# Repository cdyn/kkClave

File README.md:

# kkClave ([wiki](https://github.com/cdyn/kkClave/wiki))
## [Korai Kitchen](https://www.koraikitchen.com/) Clave for yogurt incubation
#### Designed by [Jean Runnells](https://github.com/JERiv) @ [CDYN](https://github.com/cdyn)

This is a simple yougurt incubator that uses an arduino mega, a relay shield, and a space heater to make doi (yogurt) on a large scale in an upcycled beverege fridge. In this repository are: 
* [Fusion 360](../master/fusion) drawings for the power supply panel, the front panel, and an enclosure.
* [Eagle](../master/eagle) sketch of basic circuit diagram for logic and power supply including relevant shields
* [Arduino](../master/arduino) main program code

## See the [wiki](https://github.com/cdyn/kkClave/wiki) for installtion, fabrication, and use details.

## TODO:
*  implement ethernet
*  add cooling cycle features
*  handle clock overflow

[**Custom Dynamics**](https://www.customdyn.com) © [*GNU General Public License v3.0*](https://github.com/cdyn/kkClave/blob/master/LICENSE)

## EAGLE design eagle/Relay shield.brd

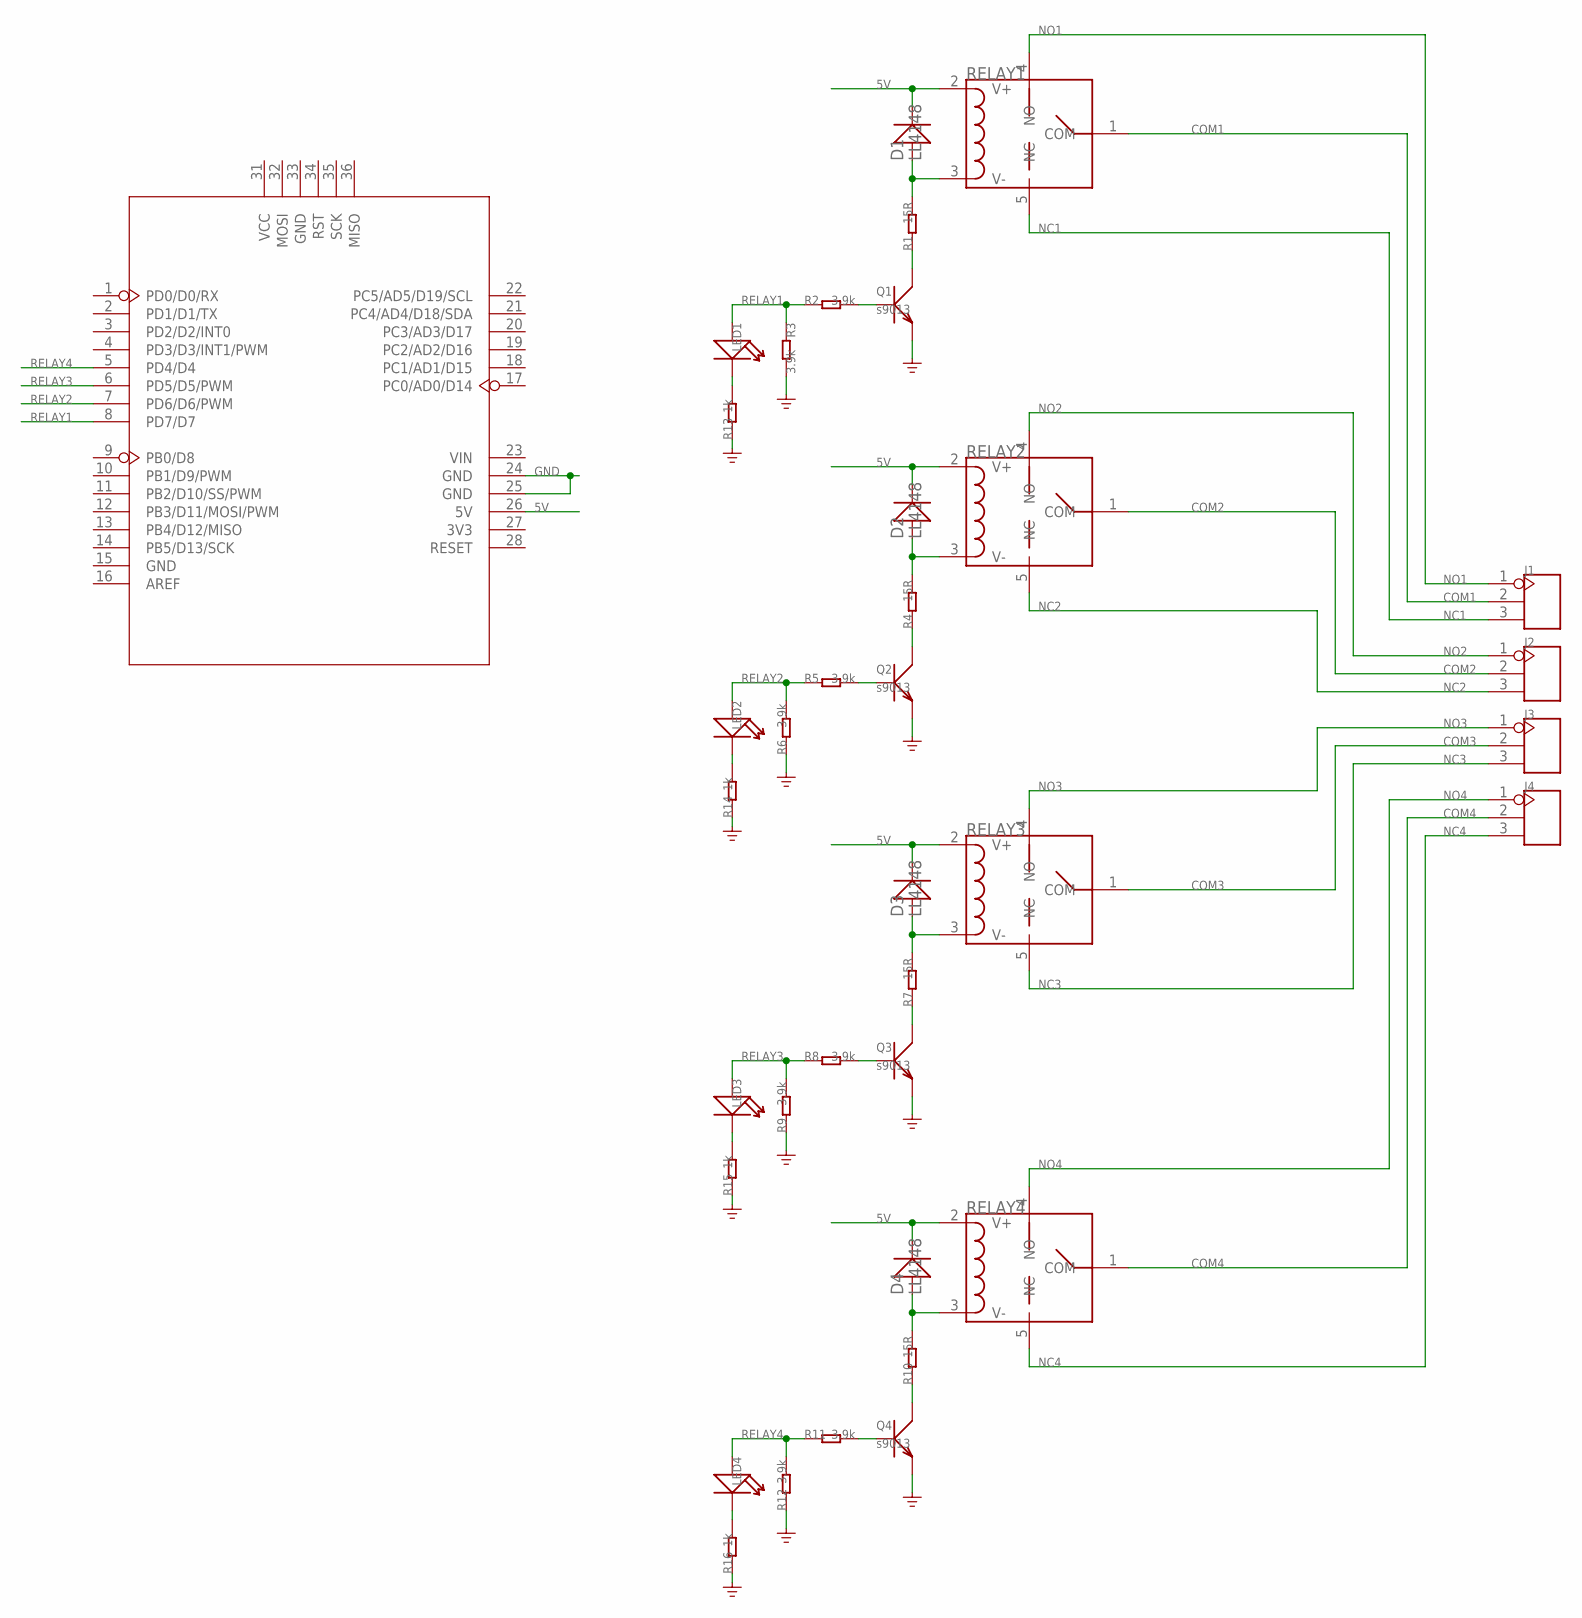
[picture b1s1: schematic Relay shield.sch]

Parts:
D1, D2, D3, D4: LL4148; D1206
J1, J2, J3, J4: SCREW-TERMINAL-3P'5.08'; 3P-5.08
LED1, LED2, LED3, LED4: LED'0603'; LED-0603
Q1, Q2, Q3, Q4: s9013; SOT23
R1, R4, R7, R10: 15R; R0603
R2, R3, R5, R6, R8, R9, R11, R12: 3.9k; R0603
R13, R14, R15, R16: 1k; R0603
RELAY1, RELAY2, RELAY3, RELAY4: RELAY-HLS8L-DC5V-S-C; 5P-19.0X15.5X15.8H
U1: ARDUINO'W/O-SILK'; ARDUINO-W/O-SILK

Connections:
5V: D1.-, D2.-, D3.-, D4.-, RELAY1.2 (V+), RELAY2.2 (V+), RELAY3.2 (V+), RELAY4.2 (V+), U1.26 (5V)
COM1: J1.2, RELAY1.1 (COM)
COM2: J2.2, RELAY2.1 (COM)
COM3: J3.2, RELAY3.1 (COM)
COM4: J4.2, RELAY4.1 (COM)
GND: Q1.2 (E), Q2.2 (E), Q3.2 (E), Q4.2 (E), R3.2, R6.1, R9.1, R12.1, R13.1, R14.1, R15.1, R16.1, U1.24 (GND), U1.25 (GND)
unnamed: D2.+, R4.2, RELAY2.3 (V-)
unnamed: D3.+, R7.2, RELAY3.3 (V-)
unnamed: D4.+, R10.2, RELAY4.3 (V-)
unnamed: Q1.3 (C), R1.1
unnamed: Q2.3 (C), R4.1
unnamed: Q4.1 (B), R11.2
unnamed: D1.+, R1.2, RELAY1.3 (V-)
unnamed: Q3.3 (C), R7.1
unnamed: Q4.3 (C), R10.1
unnamed: Q3.1 (B), R8.2
unnamed: LED1.-, R13.2
unnamed: LED2.-, R14.2
unnamed: LED3.-, R15.2
unnamed: LED4.-, R16.2
unnamed: Q2.1 (B), R5.2
unnamed: Q1.1 (B), R2.2
NC1: J1.3, RELAY1.5 (NC)
NC2: J2.3, RELAY2.5 (NC)
NC3: J3.3, RELAY3.5 (NC)
NC4: J4.3, RELAY4.5 (NC)
NO1: J1.1, RELAY1.4 (NO)
NO2: J2.1, RELAY2.4 (NO)
NO3: J3.1, RELAY3.4 (NO)
NO4: J4.1, RELAY4.4 (NO)
RELAY1: LED1.+, R2.1, R3.1, U1.8 (PD7/D7)
RELAY2: LED2.+, R5.1, R6.2, U1.7 (PD6/D6/PWM)
RELAY3: LED3.+, R8.1, R9.2, U1.6 (PD5/D5/PWM)
RELAY4: LED4.+, R11.1, R12.2, U1.5 (PD4/D4)

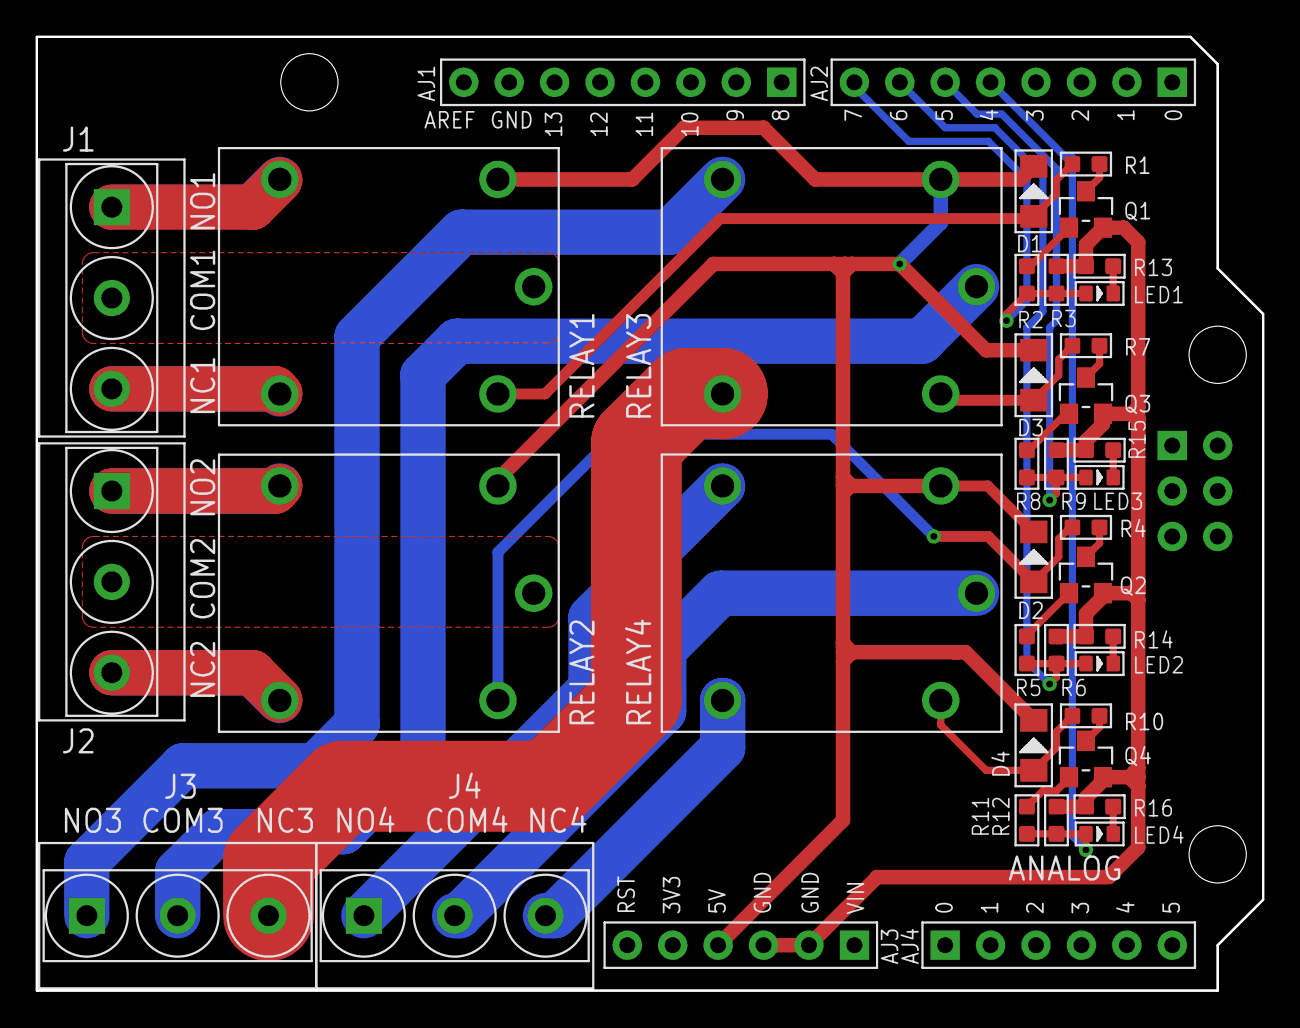
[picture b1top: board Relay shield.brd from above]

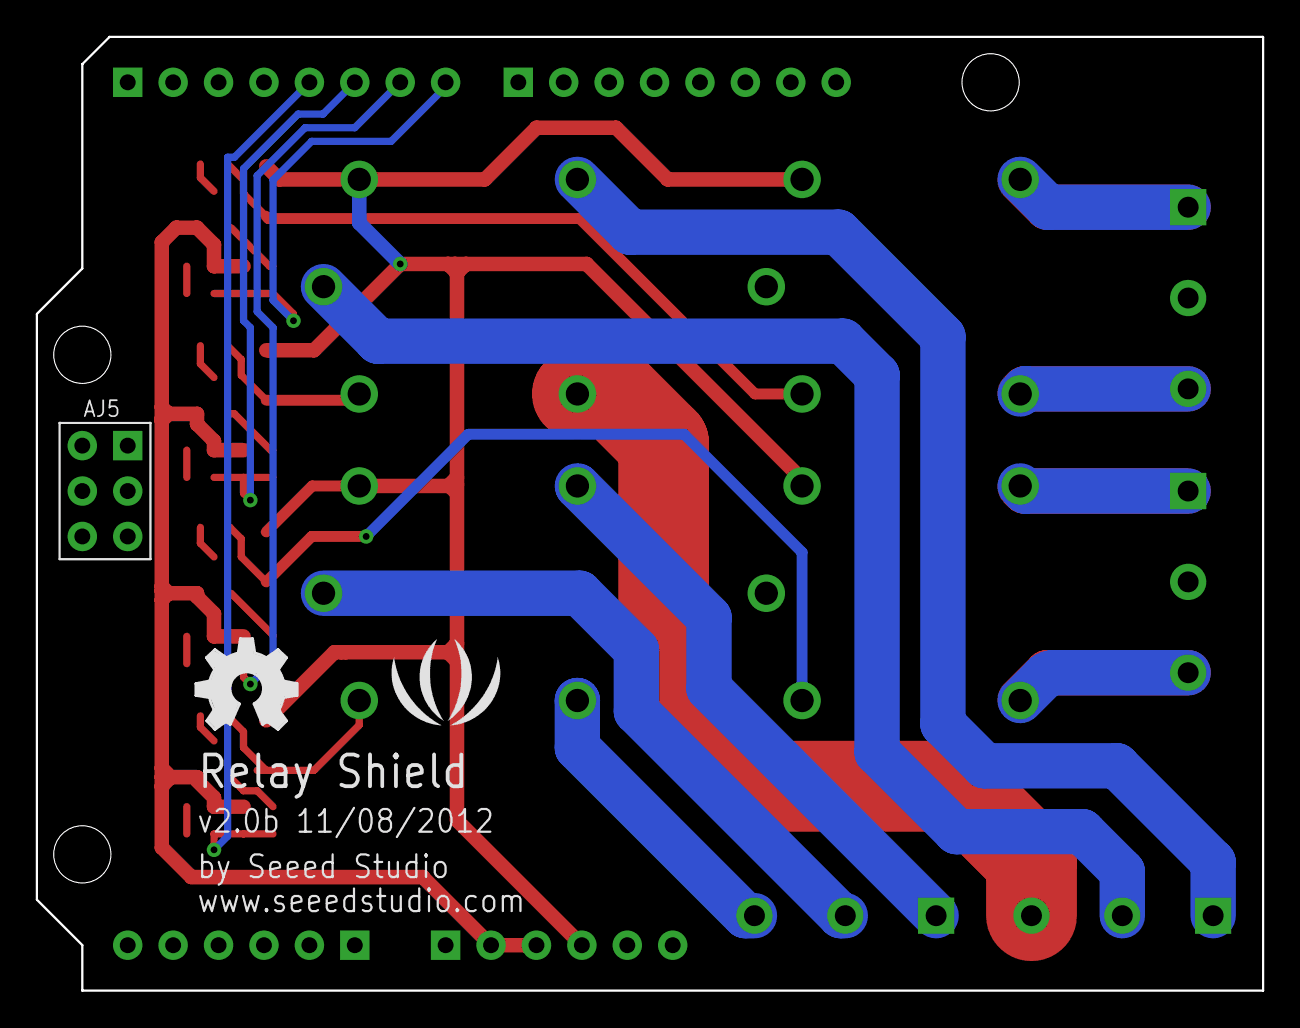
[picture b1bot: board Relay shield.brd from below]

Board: 2 copper layers, 68.6 x 53.3 mm, 39 parts (2 on the bottom side), 34 nets.

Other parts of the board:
U$13: LOGO_SILK
U$14: OSHW_FILLX200_NOTEXT

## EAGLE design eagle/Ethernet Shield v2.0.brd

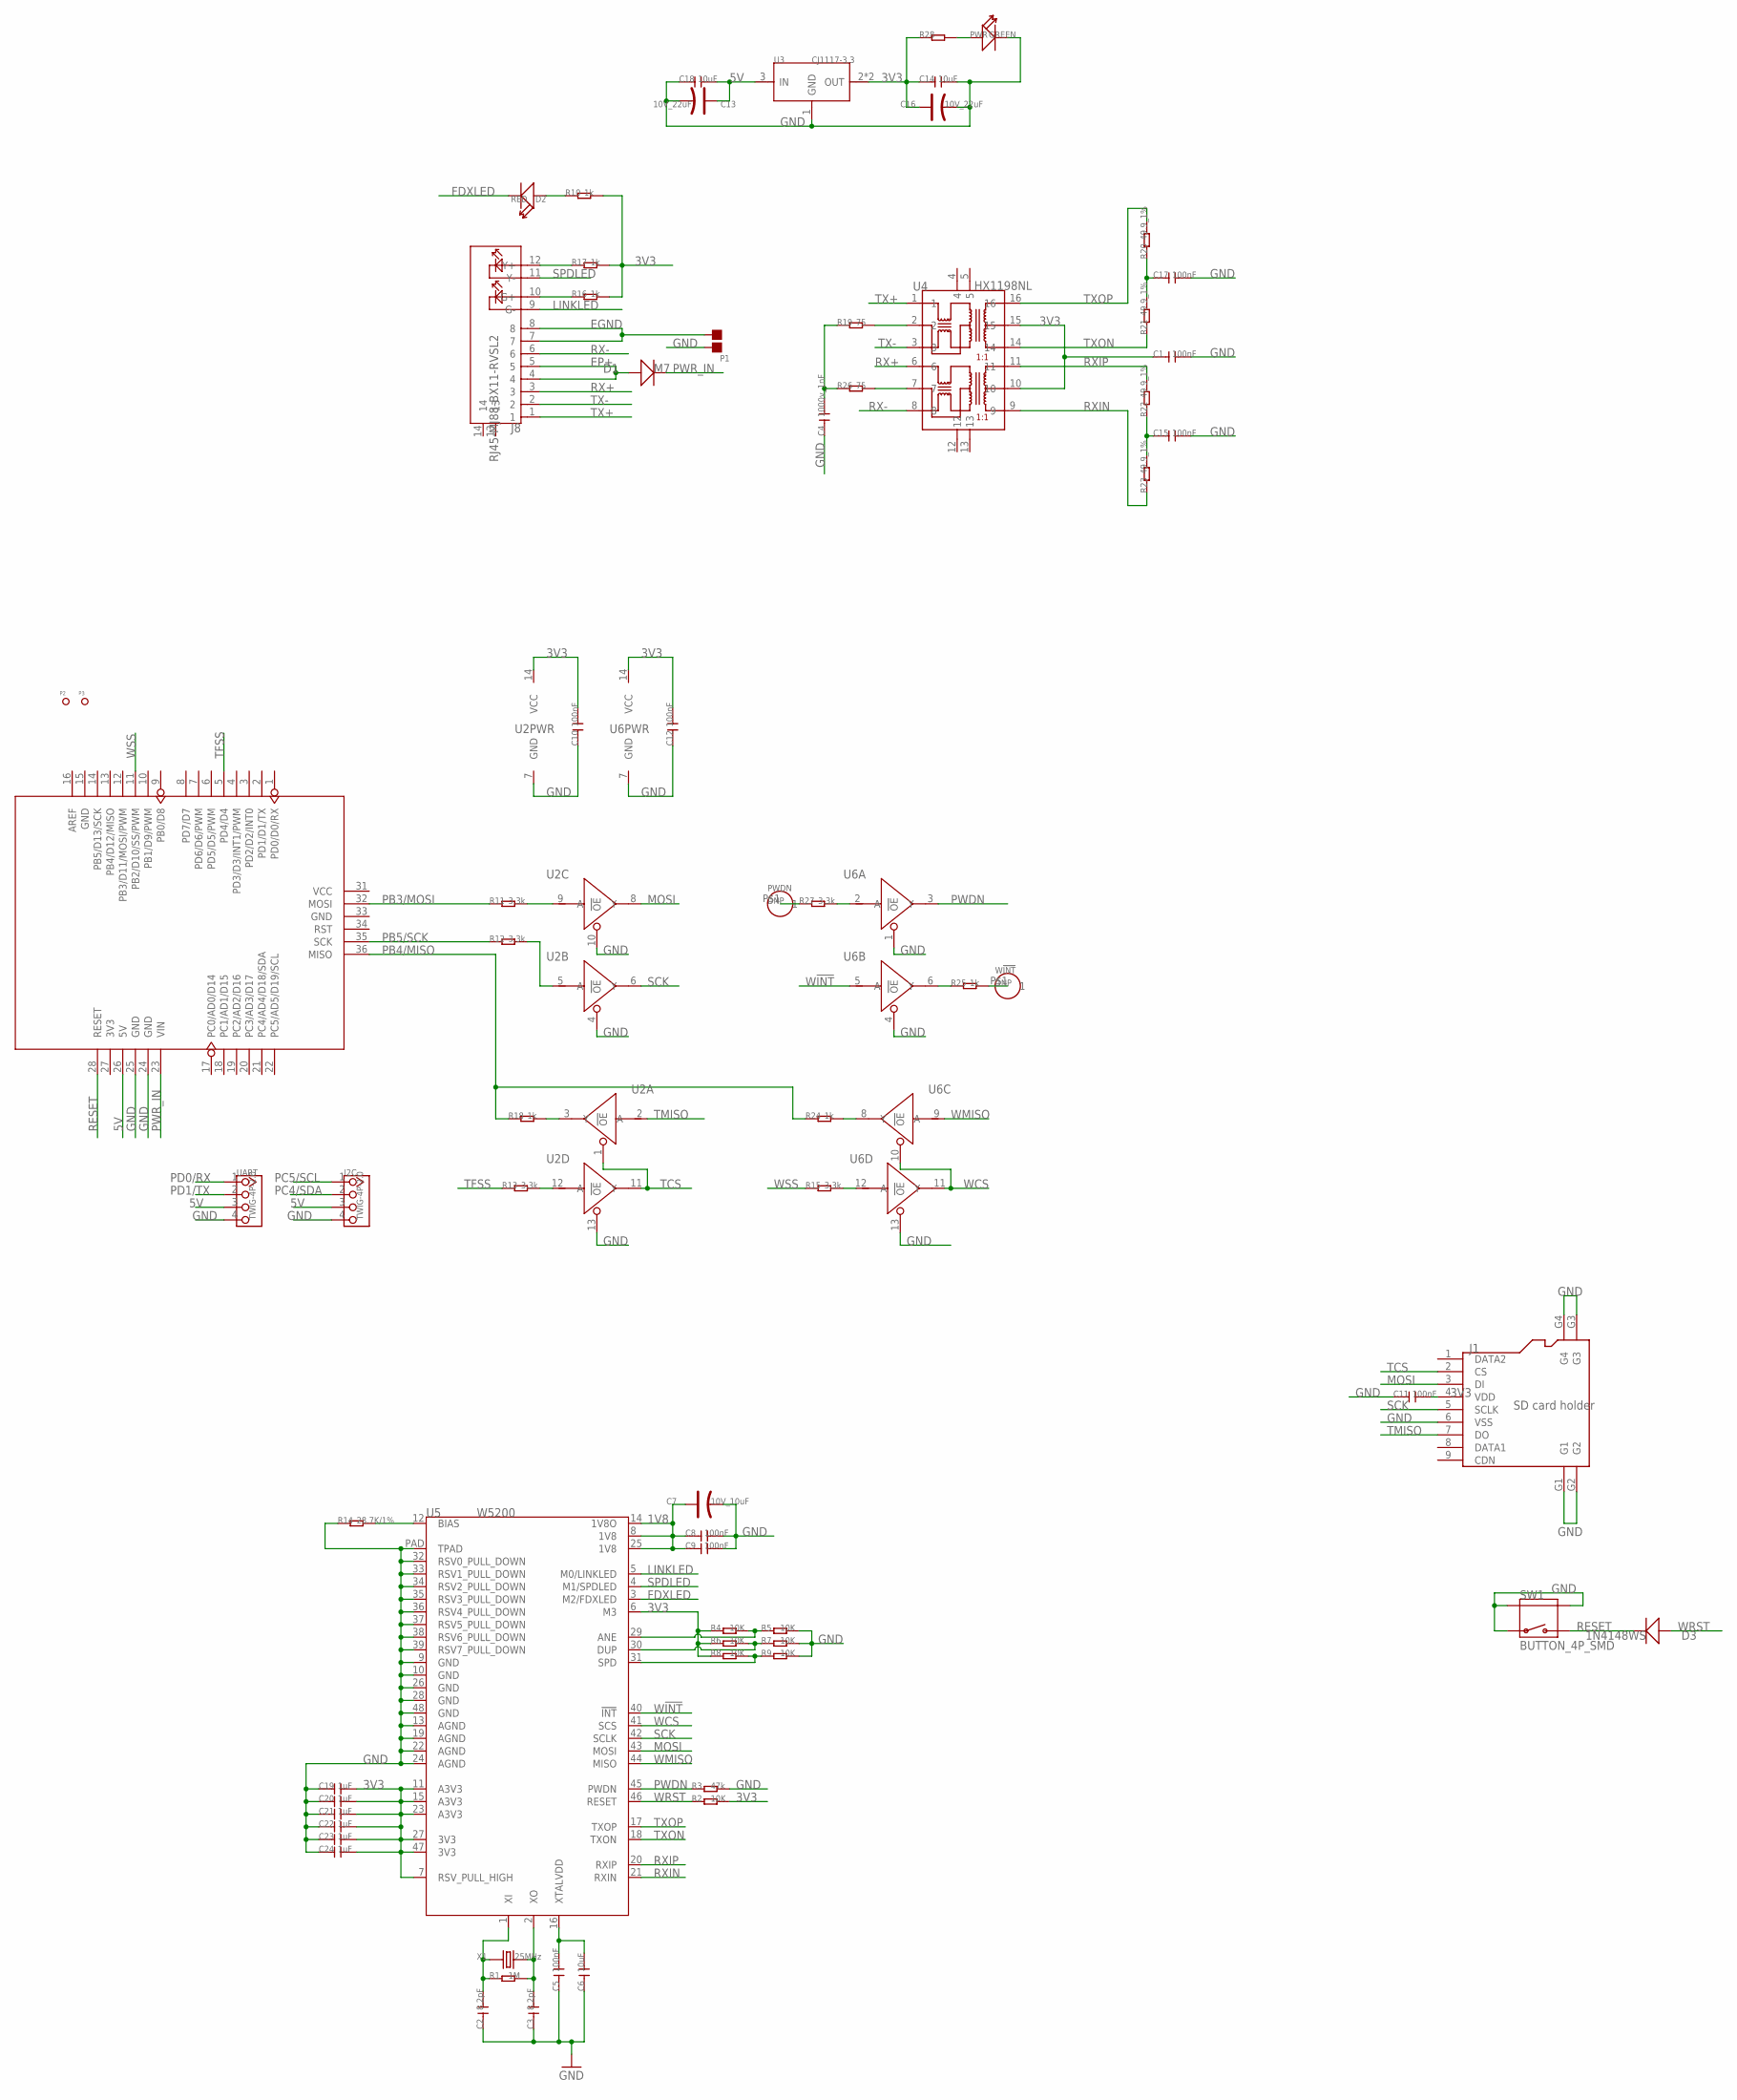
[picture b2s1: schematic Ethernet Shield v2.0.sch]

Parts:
C1, C5, C8, C9, C10, C11, C12, C15, C17: 100nF; C0603
C2, C3: 8.2pF; C0603
C4: 1000v_1nF; C1206
C6, C14, C18: 10uF; C0805
C7: 10V_10uF; AVX-A
C13, C16: 10V_22uF; AVX-B
C19, C20, C21, C22, C23, C24: 1uF; C0805
D1: M7; D2010
D2: RED; LED-0603
D3: 1N4148WS; SOD323
I2C: TWIG-4P-2.0; 4P-2.0
J1: SD card holder; 9P-SMD-W/-RING
J8: RJ45-MJ88-BX11-RVSL2
P1: DNP; 2P-SMD-1.78X1.27
P2, P3: PAD-MARK; ROUND-MARK-1.0
PWDN: DNP; 1P-65/35MIL
PWR: GREEN; LED-0603
R1: 1M; R0603
R2, R4, R5, R6, R7, R8, R9: 10K; R0603
R3: 47k; R0603
R10, R16, R17, R18, R24, R25: 1k; R0603
R11, R12, R13, R15, R27: 3.3k; R0603
R14: 28.7K/1%; R0603
R19, R26: 75; R0603
R20, R21, R22, R23: 49.9_1%; R0603
R28: R-0603; R0603
SW1: BUTTON_4P_SMD; 4P-SMD-7X3.5X3.5
U1: ARDUINO
U2, U6: 74VHC125PW; TSSOP14
U3: CJ1117-3.3; SOT-223
U4: HX1198NL; SOIC16-9.53
U5: W5200; QFN48
UART: TWIG-4P-2.0; 4P-2.0
W!INT: DNP; 1P-65/35MIL
X1: 25MHz; 2P-SMD-5X3.2

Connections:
1V8: C7.+, C8.1, C9.1, U5.8 (1V8), U5.14 (1V8O), U5.25 (1V8)
3V3: C1.1, C10.2, C11.2, C12.2, C14.1, C16.+, C19.2, C20.2, C21.2, C22.2, C23.2, C24.2, J1.4 (VDD), R2.2, R4.1, R6.1, R8.1, R10.2, R16.2, R17.2, R28.1, U2.14 (VCC), U3.2 (OUT), U3.TER (OUT), U4.10, U4.15, U5.6 (M3), U5.7 (RSV_PULL_HIGH), U5.11 (A3V3), U5.15 (A3V3), U5.23 (A3V3), U5.27 (3V3), U5.47 (3V3), U6.14 (VCC)
5V: C13.+, C18.2, I2C.3, U1.26 (5V), U3.3 (IN), UART.3
EGND: J8.7, J8.8, P1.1
EP+: D1.+, J8.4, J8.5
FDXLED: D2.-, U5.3 (M2/FDXLED)
GND: C1.2, C2.1, C3.1, C4.1, C5.1, C6.1, C7.-, C8.2, C9.2, C10.1, C11.1, C12.1, C13.-, C14.2, C15.2, C16.-, C17.2, C18.1, C19.1, C20.1, C21.1, C22.1, C23.1, C24.1, I2C.4, J1.6 (VSS), J1.G1, J1.G2, J1.G3, J1.G4, P1.2, PWR.-, R3.2, R5.2, R7.2, R9.2, R14.1, SW1.1, SW1.S1, SW1.S2, U1.24 (GND), U1.25 (GND), U2.4 (!OE), U2.7 (GND), U2.10 (!OE), U2.13 (!OE), U3.1 (GND), U5.9 (GND), U5.10 (GND), U5.13 (AGND), U5.19 (AGND), U5.22 (AGND), U5.24 (AGND), U5.26 (GND), U5.28 (GND), U5.32 (RSV0_PULL_DOWN), U5.33 (RSV1_PULL_DOWN), U5.34 (RSV2_PULL_DOWN), U5.35 (RSV3_PULL_DOWN), U5.36 (RSV4_PULL_DOWN), U5.37 (RSV5_PULL_DOWN), U5.38 (RSV6_PULL_DOWN), U5.39 (RSV7_PULL_DOWN), U5.48 (GND), U5.PAD (TPAD), U6.1 (!OE), U6.4 (!OE), U6.7 (GND), U6.13 (!OE), UART.4
LINKLED: J8.9 (G-), U5.5 (M0/LINKLED)
MOSI: J1.3 (DI), U2.8 (Y), U5.43 (MOSI)
unnamed: C2.2, R1.1, U5.1 (XI), X1.1
unnamed: C3.2, R1.2, U5.2 (XO), X1.2
unnamed: R4.2, R5.1, U5.29 (ANE)
unnamed: R6.2, R7.1, U5.30 (DUP)
unnamed: R8.2, R9.1, U5.31 (SPD)
unnamed: D2.+, R10.1
unnamed: R12.2, U2.5 (A)
unnamed: R11.2, U2.9 (A)
unnamed: R13.2, U2.12 (A)
unnamed: R15.2, U6.12 (A)
unnamed: R26.2, U4.7
unnamed: R19.2, U4.2
unnamed: C4.2, R19.1, R26.1
unnamed: R18.2, U2.3 (Y)
unnamed: C15.1, R22.1, R23.2
unnamed: C17.1, R20.1, R21.2
unnamed: R24.2, U6.8 (Y)
unnamed: J8.12 (Y+), R17.1
unnamed: J8.10 (G+), R16.1
unnamed: R25.1, U6.6 (Y)
unnamed: R25.2, W!INT.P$1
unnamed: C5.2, C6.2, U5.16 (XTALVDD)
unnamed: R14.2, U5.12 (BIAS)
unnamed: R27.2, U6.2 (A)
unnamed: PWDN.P$1, R27.1
unnamed: PWR.+, R28.2
PB3/MOSI: R11.1, U1.32 (MOSI)
PB4/MISO: R18.1, R24.1, U1.36 (MISO)
PB5/SCK: R12.1, U1.35 (SCK)
PC4/SDA: I2C.2
PC5/SCL: I2C.1
PD0/RX: UART.1
PD1/TX: UART.2
PWDN: R3.1, U5.45 (PWDN), U6.3 (Y)
PWR_IN: D1.-, U1.23 (VIN)
RESET: D3.-, SW1.2, U1.28 (RESET)
RX+: J8.3, U4.6
RX-: J8.6, U4.8
RXIN: R23.1, U4.9, U5.21 (RXIN)
RXIP: R22.2, U4.11, U5.20 (RXIP)
SCK: J1.5 (SCLK), U2.6 (Y), U5.42 (SCLK)
SPDLED: J8.11 (Y-), U5.4 (M1/SPDLED)
TCS: J1.2 (CS), U2.1 (!OE), U2.11 (Y)
TFSS: R13.1, U1.5 (PD4/D4)
TMISO: J1.7 (DO), U2.2 (A)
TX+: J8.1, U4.1
TX-: J8.2, U4.3
TXON: R21.1, U4.14, U5.18 (TXON)
TXOP: R20.2, U4.16, U5.17 (TXOP)
W!INT: U5.40 (!INT), U6.5 (A)
WCS: U5.41 (SCS), U6.10 (!OE), U6.11 (Y)
WMISO: U5.44 (MISO), U6.9 (A)
WRST: D3.+, R2.1, U5.46 (RESET)
WSS: R15.1, U1.11 (PB2/D10/SS/PWM)

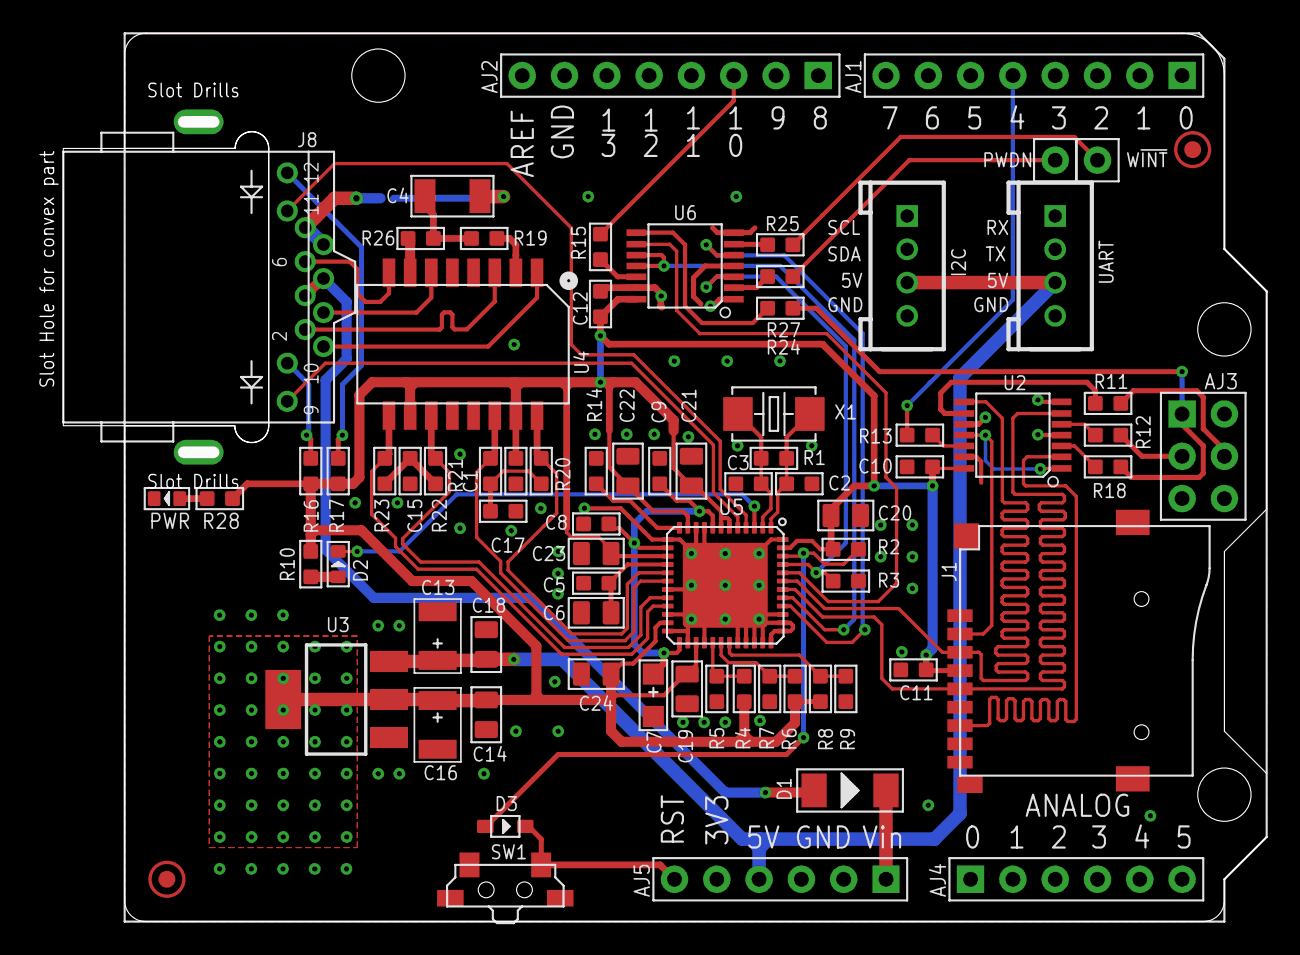
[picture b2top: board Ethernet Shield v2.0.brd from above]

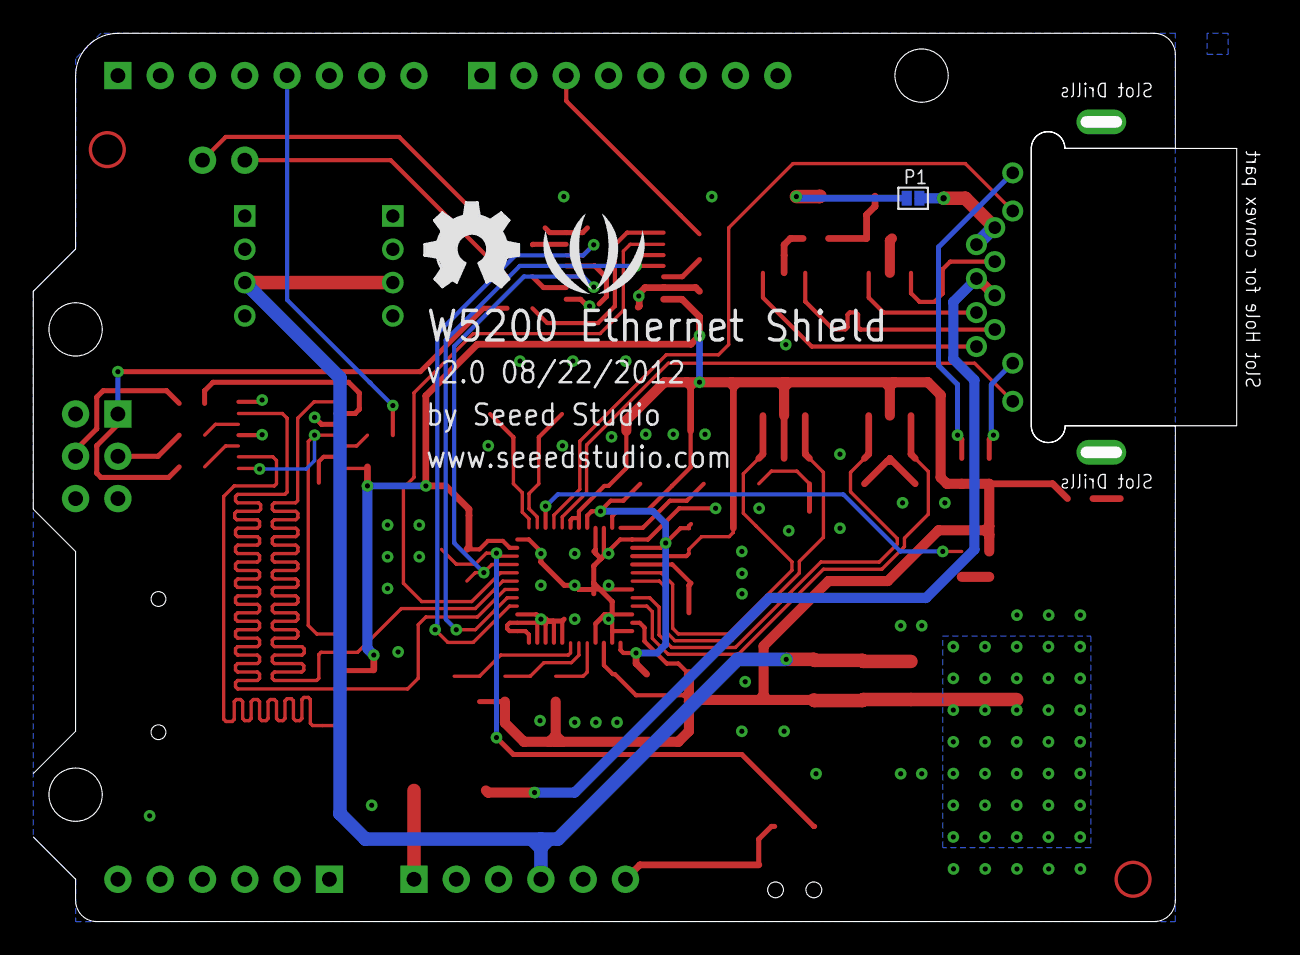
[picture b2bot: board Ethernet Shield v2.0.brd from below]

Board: 2 copper layers, 73.4 x 52.6 mm, 75 parts (3 on the bottom side), 59 nets.

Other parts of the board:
U$1: LOGO_SILK
U$2: OSHW_FILLX200_NOTEXT

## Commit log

2019-04-15 pinout and arduino
2019-09-12 Updated code and added drawings
2019-09-13 code RC1
    fished:
    Standby
    Holdown race
    Fan cont
    Light cont
2019-09-13 Create LICENSE
2019-09-13 update comments
2019-09-13 build notes images
2019-10-01 Update arduino_sketch.ino
    commented code

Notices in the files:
parts and their libraries:
SparkFun: Licensing: CC v3.0 Share-Alike You are welcome to use this library for commercial purposes.
